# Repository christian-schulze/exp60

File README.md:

# Exp60 - An opinionated 60% with arrow keys PCB

---

> **Warning** WIP - Functioning prototype not built yet.
>
> - Components ordered (2023-01-06).
> - PCB's ordered (2023-01-07).

[Link to Keyboard Layout Editor project](http://www.keyboard-layout-editor.com/#/gists/84f70adc6e3be321baacc794c3d78efd)

## Why?

I've always preferred the size of a 60%, but never managed to kick the arrow key addiction. Having tried the `dz60` and `dz64` from kbdfans (dz64 being my fav), they both have trade-offs I've never been quite happy with.

## Design constraints

1. 60% form factor, roughly the same size as a GH60.
2. Arrow cluster
3. Standard 2.25U left shift
4. Standard 1U forward slash / question mark key
5. Bottom row should have `CTRL`, `Fn`, `GUI`, `ALT` and `HYPER` keys
6. USB-C
7. Hot-swap
8. Hand solderable

## How was this layout chosen?

In order to meet design constraints 2, 3 and 4, the arrow cluster needs to be located next to the forward slash key. The right arrow key only has 0.75U of space to its right, so we have the `HHKB-esque` gaps at the edges of the bottom row.

To meet design constraint 5, the space bar needs to be shrunk to 2.75U. I've been daily driving a heavily modded `HHKB Pro JP` since 2017 so this is A-OK to me.

## PCB Design choices

1. All SMD components due to limited space.
2. Use `atmega32u2-au` MCU instead of `atmega32u4-au` due to limited space (32 vs 48 pins).
3. Large footprint SMD components so everything is more easily hand solderable.

## Acknowledgements

- [JP60 by ai03](https://github.com/ai03-2725/JP60)

  60%, USB-C, ESD and over voltage/currrent protection.

- [Keyboard Matías](https://github.com/nstrappazzonc/keyboard)

  This uses the `atmega32u2-au`, which is crucial for fitting the MCU and related traces on my PCB.

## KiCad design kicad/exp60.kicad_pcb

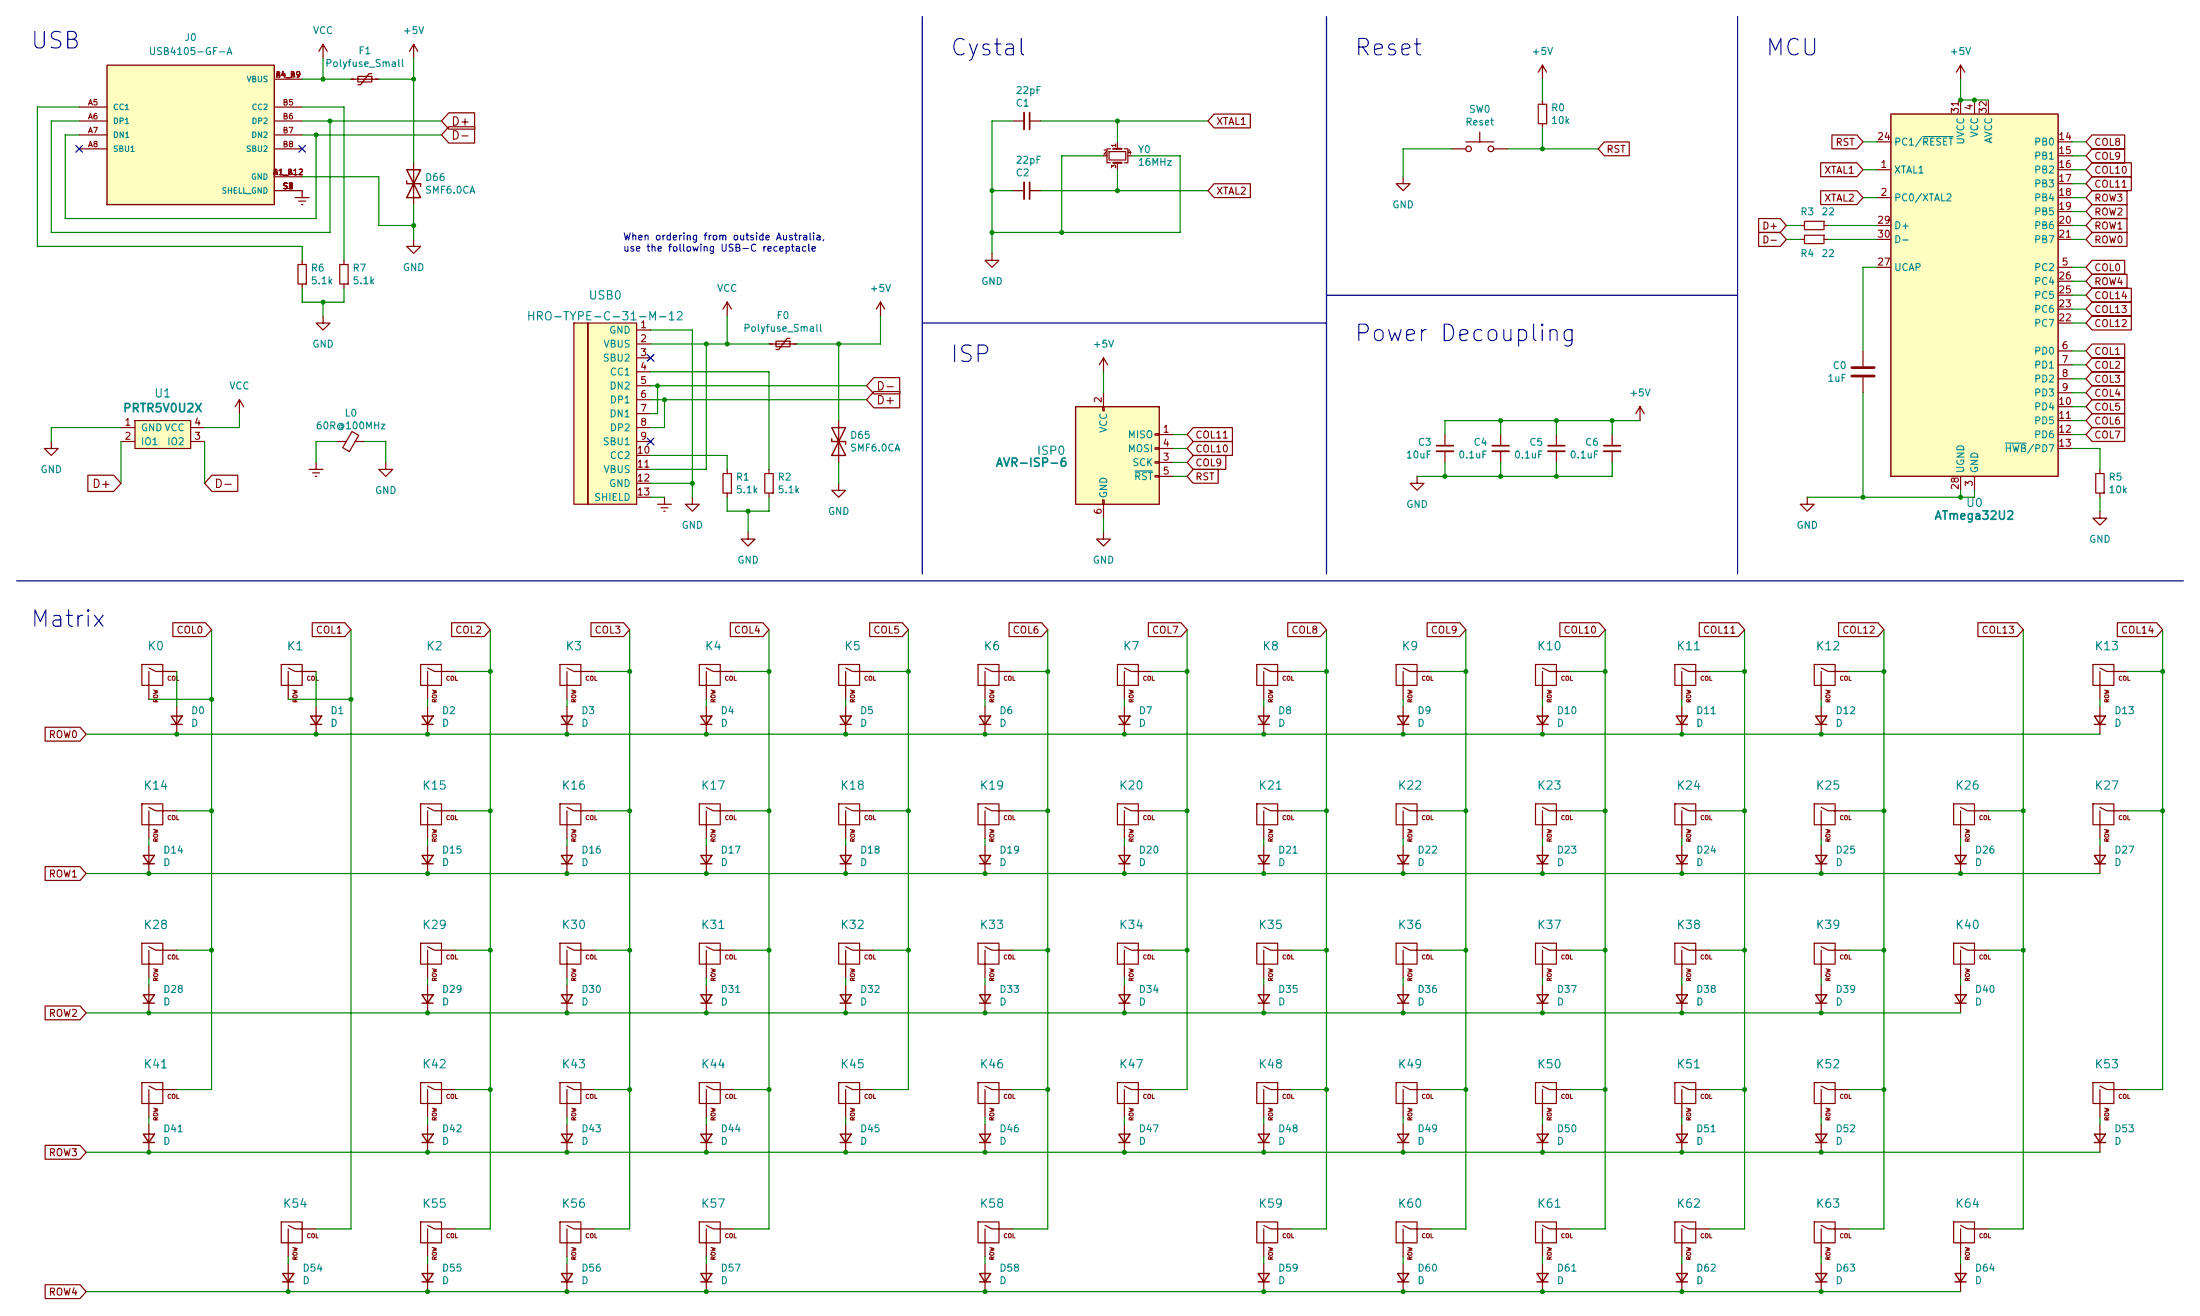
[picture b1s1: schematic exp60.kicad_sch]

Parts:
C0: 1uF; C_0805_2012Metric
C1, C2: 22pF; C_0805_2012Metric
C3: 10uF; C_0805_2012Metric
C4, C5, C6: 0.1uF; C_0805_2012Metric
D0, D1, D2, D3, D4, D5, D6, D7, D8, D9, D10, D11, D12, D13, D14, D15, D16, D17, D18, D19, D20, D21, D22, D23, D24, D25, D26, D27, D28, D29, D30, D31, D32, D33, D34, D35, D36, D37, D38, D39, D40, D41, D42, D43, D44, D45, D46, D47, D48, D49, D50, D51, D52, D53, D54, D55, D56, D57, D58, D59, D60, D61, D62, D63, D64: D; D_SOD-123
D65, D66: SMF6.0CA; D_SOD-123
F0, F1: Polyfuse_Small; Fuse_1206_3216Metric
ISP0: AVR-ISP-6; CON_TC2030_outlined
J0: USB4105-GF-A; GCT_USB4105-GF-A-HandSoldering; PARTREV A3
K0, K1, K2, K3, K4, K5, K6, K7, K8, K9, K10, K11, K12, K15, K16, K17, K18, K19, K20, K21, K22, K23, K24, K25, K26, K29, K30, K31, K32, K33, K34, K35, K36, K37, K38, K39, K42, K43, K44, K45, K46, K47, K48, K49, K50, K51, K52, K55, K56, K60, K61, K62, K63, K64: KEYSW; MXOnly-1U-Hotswap
K13: KEYSW; MXOnly-2U-Hotswap
K14, K27: KEYSW; MXOnly-1.5U-Hotswap
K28, K53: KEYSW; MXOnly-1.75U-Hotswap
K40, K41: KEYSW; MXOnly-2.25U-Hotswap
K54, K57, K59: KEYSW; MXOnly-1.25U-Hotswap
K58: KEYSW; MXOnly-2.75U-Hotswap-ReversedStabilizers
L0: 60R@100MHz; L_1206_3216Metric
R0, R5: 10k; R_0805_2012Metric
R1, R2, R6, R7: 5.1k; R_0805_2012Metric
R3, R4: 22; R_0805_2012Metric
SW0: Reset; SW_SPST_SKQG_WithStem
U0: ATmega32U2; TQFP-32_7x7mm_P0.8mm
U1: PRTR5V0U2X; SOT-143_Handsoldering
USB0: HRO-TYPE-C-31-M-12; HRO-TYPE-C-31-M-12-HandSoldering
Y0: 16MHz; Crystal_SMD_3225-4Pin_3.2x2.5mm_HandSoldering

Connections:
+5V: C3.1, C4.1, C5.1, C6.1, D65.2 (A2), D66.2 (A2), F0.1, F1.1, ISP0.2 (VCC), R0.2, U0.4 (VCC), U0.31 (UVCC), U0.32 (AVCC)
COL0: K0.2 (ROW), K14.1 (COL), K28.1 (COL), K41.1 (COL), U0.5 (PC2)
COL1: K1.2 (ROW), K54.1 (COL), U0.6 (PD0)
COL2: K2.1 (COL), K15.1 (COL), K29.1 (COL), K42.1 (COL), K55.1 (COL), U0.7 (PD1)
COL3: K3.1 (COL), K16.1 (COL), K30.1 (COL), K43.1 (COL), K56.1 (COL), U0.8 (PD2)
COL4: K4.1 (COL), K17.1 (COL), K31.1 (COL), K44.1 (COL), K57.1 (COL), U0.9 (PD3)
COL5: K5.1 (COL), K18.1 (COL), K32.1 (COL), K45.1 (COL), U0.10 (PD4)
COL6: K6.1 (COL), K19.1 (COL), K33.1 (COL), K46.1 (COL), K58.1 (COL), U0.11 (PD5)
COL7: K7.1 (COL), K20.1 (COL), K34.1 (COL), K47.1 (COL), U0.12 (PD6)
COL8: K8.1 (COL), K21.1 (COL), K35.1 (COL), K48.1 (COL), K59.1 (COL), U0.14 (PB0)
COL9: ISP0.3 (SCK), K9.1 (COL), K22.1 (COL), K36.1 (COL), K49.1 (COL), K60.1 (COL), U0.15 (PB1)
COL10: ISP0.4 (MOSI), K10.1 (COL), K23.1 (COL), K37.1 (COL), K50.1 (COL), K61.1 (COL), U0.16 (PB2)
COL11: ISP0.1 (MISO), K11.1 (COL), K24.1 (COL), K38.1 (COL), K51.1 (COL), K62.1 (COL), U0.17 (PB3)
COL12: K12.1 (COL), K25.1 (COL), K39.1 (COL), K52.1 (COL), K63.1 (COL), U0.22 (PC7)
COL13: K26.1 (COL), K40.1 (COL), K64.1 (COL), U0.23 (PC6)
COL14: K13.1 (COL), K27.1 (COL), K53.1 (COL), U0.25 (PC5)
D+: J0.A6 (DP1), J0.B6 (DP2), R3.2, U1.2 (IO1), USB0.6 (DP1), USB0.8 (DP2)
D-: J0.A7 (DN1), J0.B7 (DN2), R4.2, U1.3 (IO2), USB0.5 (DN2), USB0.7 (DN1)
Earth: J0.S1 (SHELL_GND), J0.S2 (SHELL_GND), J0.S3 (SHELL_GND), J0.S4 (SHELL_GND), L0.1, USB0.13 (SHIELD)
GND: C0.2, C1.2, C2.2, C3.2, C4.2, C5.2, C6.2, D65.1 (A1), D66.1 (A1), ISP0.6 (GND), J0.A1_B12 (GND), J0.B1_A12 (GND), L0.2, R1.1, R2.1, R5.1, R6.1, R7.1, SW0.2, U0.3 (GND), U0.28 (UGND), U1.1 (GND), USB0.1 (GND), USB0.12 (GND), Y0.2, Y0.4
unnamed: C0.1, U0.27 (UCAP)
unnamed: D0.2 (A), K0.1 (COL)
unnamed: D1.2 (A), K1.1 (COL)
unnamed: D2.2 (A), K2.2 (ROW)
unnamed: D3.2 (A), K3.2 (ROW)
unnamed: D4.2 (A), K4.2 (ROW)
unnamed: D5.2 (A), K5.2 (ROW)
unnamed: D6.2 (A), K6.2 (ROW)
unnamed: D7.2 (A), K7.2 (ROW)
unnamed: D8.2 (A), K8.2 (ROW)
unnamed: D9.2 (A), K9.2 (ROW)
unnamed: D10.2 (A), K10.2 (ROW)
unnamed: D11.2 (A), K11.2 (ROW)
unnamed: D12.2 (A), K12.2 (ROW)
unnamed: D13.2 (A), K13.2 (ROW)
unnamed: D14.2 (A), K14.2 (ROW)
unnamed: D15.2 (A), K15.2 (ROW)
unnamed: D16.2 (A), K16.2 (ROW)
unnamed: D17.2 (A), K17.2 (ROW)
unnamed: D18.2 (A), K18.2 (ROW)
unnamed: D19.2 (A), K19.2 (ROW)
unnamed: D20.2 (A), K20.2 (ROW)
unnamed: D21.2 (A), K21.2 (ROW)
unnamed: D22.2 (A), K22.2 (ROW)
unnamed: D23.2 (A), K23.2 (ROW)
unnamed: D24.2 (A), K24.2 (ROW)
unnamed: D25.2 (A), K25.2 (ROW)
unnamed: D26.2 (A), K26.2 (ROW)
unnamed: D27.2 (A), K27.2 (ROW)
unnamed: D28.2 (A), K28.2 (ROW)
unnamed: D29.2 (A), K29.2 (ROW)
unnamed: D30.2 (A), K30.2 (ROW)
unnamed: D31.2 (A), K31.2 (ROW)
unnamed: D32.2 (A), K32.2 (ROW)
unnamed: D33.2 (A), K33.2 (ROW)
unnamed: D34.2 (A), K34.2 (ROW)
unnamed: D35.2 (A), K35.2 (ROW)
unnamed: D36.2 (A), K36.2 (ROW)
unnamed: D37.2 (A), K37.2 (ROW)
unnamed: D38.2 (A), K38.2 (ROW)
unnamed: D39.2 (A), K39.2 (ROW)
unnamed: D40.2 (A), K40.2 (ROW)
unnamed: D41.2 (A), K41.2 (ROW)
unnamed: D42.2 (A), K42.2 (ROW)
unnamed: D43.2 (A), K43.2 (ROW)
unnamed: D44.2 (A), K44.2 (ROW)
unnamed: D45.2 (A), K45.2 (ROW)
unnamed: D46.2 (A), K46.2 (ROW)
unnamed: D47.2 (A), K47.2 (ROW)
unnamed: D48.2 (A), K48.2 (ROW)
unnamed: D49.2 (A), K49.2 (ROW)
unnamed: D50.2 (A), K50.2 (ROW)
unnamed: D51.2 (A), K51.2 (ROW)
unnamed: D52.2 (A), K52.2 (ROW)
unnamed: D53.2 (A), K53.2 (ROW)
unnamed: D54.2 (A), K54.2 (ROW)
unnamed: D55.2 (A), K55.2 (ROW)
unnamed: D56.2 (A), K56.2 (ROW)
unnamed: D57.2 (A), K57.2 (ROW)
unnamed: D58.2 (A), K58.2 (ROW)
unnamed: D59.2 (A), K59.2 (ROW)
unnamed: D60.2 (A), K60.2 (ROW)
unnamed: D61.2 (A), K61.2 (ROW)
unnamed: D62.2 (A), K62.2 (ROW)
unnamed: D63.2 (A), K63.2 (ROW)
unnamed: D64.2 (A), K64.2 (ROW)
unnamed: J0.A5 (CC1), R6.2
unnamed: J0.B5 (CC2), R7.2
unnamed: R1.2, USB0.10 (CC2)
unnamed: R2.2, USB0.4 (CC1)
unnamed: R3.1, U0.29 (D+)
unnamed: R4.1, U0.30 (D-)
unnamed: R5.2, U0.13 (~HWB/PD7)
ROW0: D0.1 (K), D1.1 (K), D2.1 (K), D3.1 (K), D4.1 (K), D5.1 (K), D6.1 (K), D7.1 (K), D8.1 (K), D9.1 (K), D10.1 (K), D11.1 (K), D12.1 (K), D13.1 (K), U0.21 (PB7)
ROW1: D14.1 (K), D15.1 (K), D16.1 (K), D17.1 (K), D18.1 (K), D19.1 (K), D20.1 (K), D21.1 (K), D22.1 (K), D23.1 (K), D24.1 (K), D25.1 (K), D26.1 (K), D27.1 (K), U0.20 (PB6)
ROW2: D28.1 (K), D29.1 (K), D30.1 (K), D31.1 (K), D32.1 (K), D33.1 (K), D34.1 (K), D35.1 (K), D36.1 (K), D37.1 (K), D38.1 (K), D39.1 (K), D40.1 (K), U0.19 (PB5)
ROW3: D41.1 (K), D42.1 (K), D43.1 (K), D44.1 (K), D45.1 (K), D46.1 (K), D47.1 (K), D48.1 (K), D49.1 (K), D50.1 (K), D51.1 (K), D52.1 (K), D53.1 (K), U0.18 (PB4)
ROW4: D54.1 (K), D55.1 (K), D56.1 (K), D57.1 (K), D58.1 (K), D59.1 (K), D60.1 (K), D61.1 (K), D62.1 (K), D63.1 (K), D64.1 (K), U0.26 (PC4)
RST: ISP0.5 (~RST), R0.1, SW0.1, U0.24 (PC1/~RESET)
VCC: F0.2, F1.2, J0.A4_B9 (VBUS), J0.B4_A9 (VBUS), U1.4 (VCC), USB0.2 (VBUS), USB0.11 (VBUS)
XTAL1: C1.1, U0.1 (XTAL1), Y0.1
XTAL2: C2.1, U0.2 (PC0/XTAL2), Y0.3

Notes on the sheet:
USB
Power Decoupling
Cystal
Matrix
When ordering from outside Australia, use the following USB-C receptacle
ISP
Reset
MCU

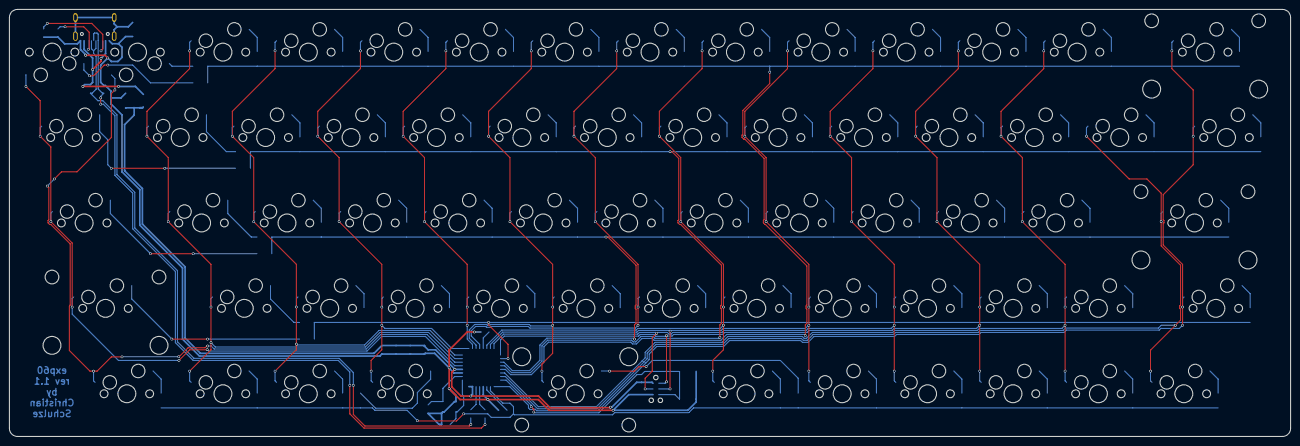
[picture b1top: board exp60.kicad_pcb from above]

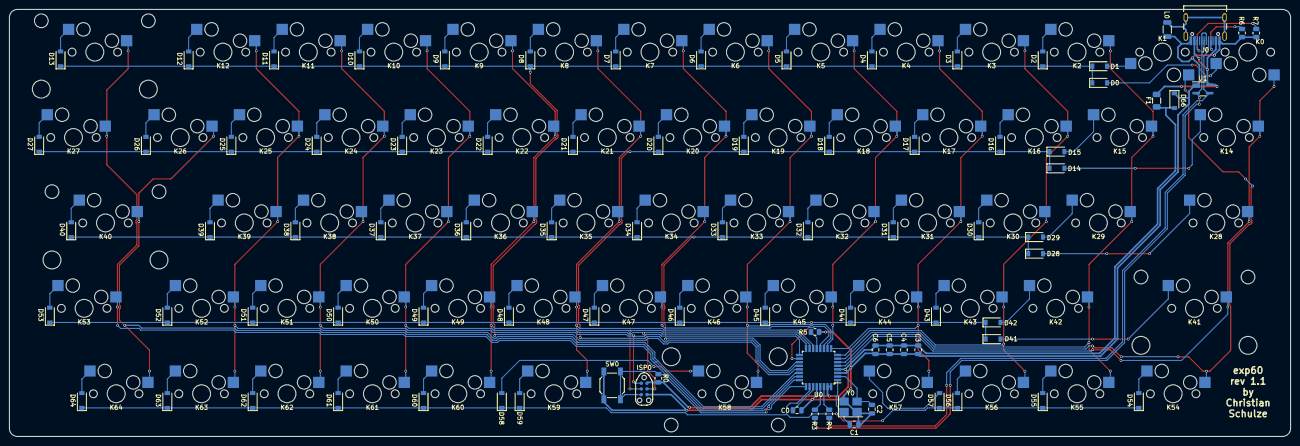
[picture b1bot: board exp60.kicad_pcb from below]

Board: 2 copper layers, 285.8 x 95.2 mm, 152 parts (87 on the bottom side), 100 nets.

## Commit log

2023-01-05 replace usb receptacle
2023-01-05 label and route cleanup
2023-01-07 generate gerbers for prototype
2023-01-19 fix ISP pins, curved corners, larger component spacing
